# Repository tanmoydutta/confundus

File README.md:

# Confundus, an LIC Super Capacitor Trinket
Confundus powers an MCU driven LED matrix by means of using an LIC Super Capacitor as it's power source.

It also has a matching 3D printed box to house the circuit as a keychain hanger or as an ornament that hangs next to an ID card

Some of the actual view of the project - 

This project is certified as Open Source Hardware - 
<p align="center">
  
</p>

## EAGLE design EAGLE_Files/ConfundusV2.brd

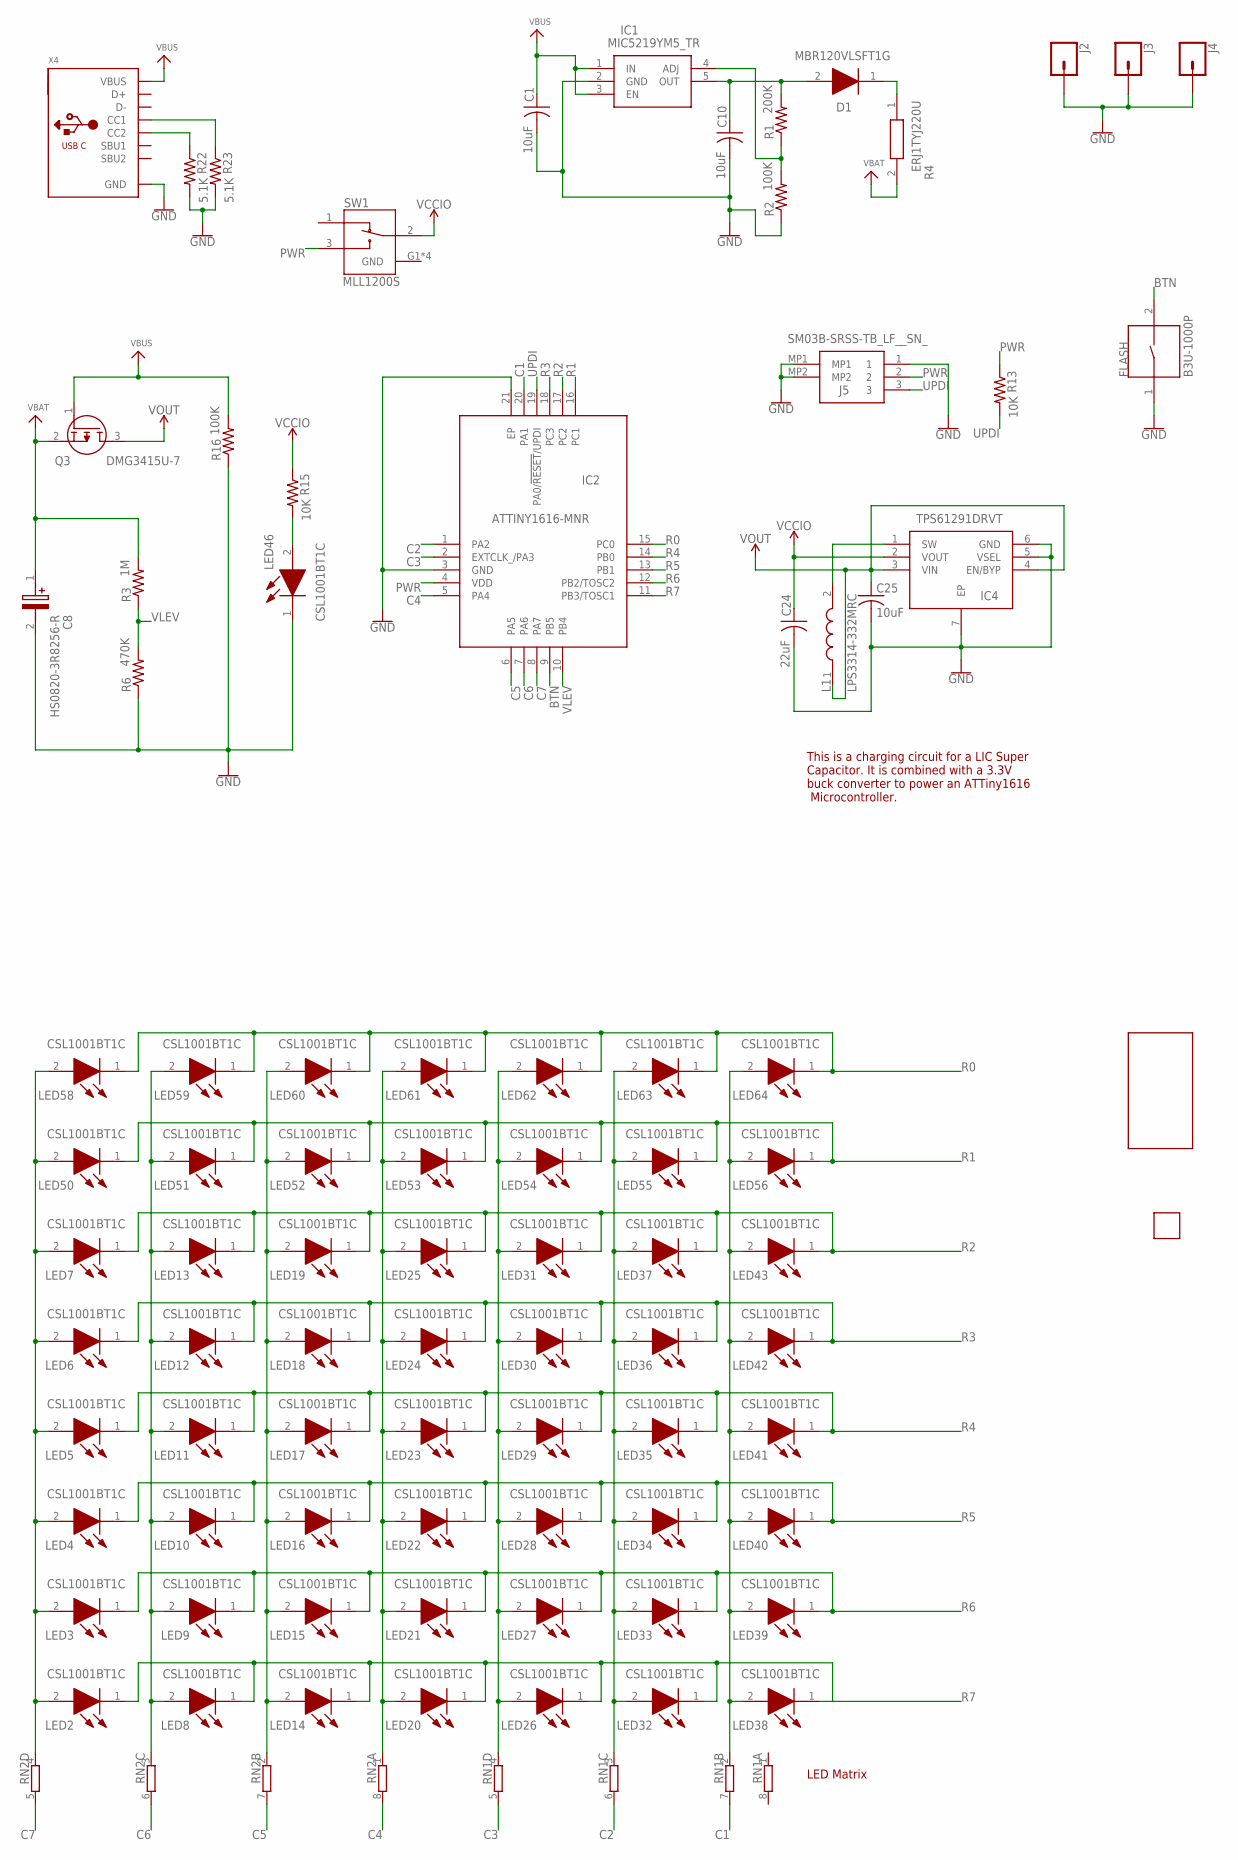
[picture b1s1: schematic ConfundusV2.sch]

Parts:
C1, C10, C25: 10uF; C0402
C8: HS0820-3R8256-R; CAPPRD350W65D850H2200
C24: 22uF; C0402
D1: MBR120VLSFT1G; SODFL3616X98N
FLASH: B3U-1000P; SW_B3U-1000P
IC1: MIC5219YM5_TR; SOT95P280X145-5N
IC2: ATTINY1616-MNR; QFN40P300X300X90-21N
IC4: TPS61291DRVT; SON65P200X200X80-7N
J2, J3, J4: CONN_01PTH_2MM; 1X01_2MM
J5: SM03B-SRSS-TB_LF__SN_; SM03BSRSSTBLFSN
L1: LPS3314-332MRC; LPS3314332MRC
LED2, LED3, LED4, LED5, LED6, LED7, LED8, LED9, LED10, LED11, LED12, LED13, LED14, LED15, LED16, LED17, LED18, LED19, LED20, LED21, LED22, LED23, LED24, LED25, LED26, LED27, LED28, LED29, LED30, LED31, LED32, LED33, LED34, LED35, LED36, LED37, LED38, LED39, LED40, LED41, LED42, LED43, LED46, LED50, LED51, LED52, LED53, LED54, LED55, LED56, LED58, LED59, LED60, LED61, LED62, LED63, LED64: CSL1001BT1C
Q3: DMG3415U-7; SOT96P240X100-3N
R1: 200K; R0402
R2, R16: 100K; R0402
R3: 1M; R0402
R4: ERJ1TYJ220U; ERJ1TRQF1R0U
R6: 470K; R0402
R13, R15: 10K; R0402
R22, R23: 5.1K; R0402
RN1, RN2: 4R-N0402ARV341; 4X0402ARV341
SW1: MLL1200S; SW_MLL1200S
U$1: SMARTT
U$2: SMARTT_SMALL
X4: MICROBUILDER_USB_C; MICROBUILDER_USB_C_CUSB31-CFM2AX-01-X

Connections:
BTN: FLASH.2, IC2.9 (PB5)
C1: IC2.20 (PA1), RN1.7 (2)
C2: IC2.1 (PA2), RN1.6 (2)
C3: IC2.2 (EXTCLK_/PA3), RN1.5 (2)
C4: IC2.5 (PA4), RN2.8 (2)
C5: IC2.6 (PA5), RN2.7 (2)
C6: IC2.7 (PA6), RN2.6 (2)
C7: IC2.8 (PA7), RN2.5 (2)
GND: C1.2, C8.2 (-), C10.2, C24.2, C25.2, FLASH.1, IC1.2 (GND), IC2.3 (GND), IC2.21 (EP), IC4.5 (VSEL), IC4.6 (GND), IC4.7 (EP), J2.1, J3.1, J4.1, J5.1, J5.MP1, J5.MP2, LED46.1 (K), R2.1, R6.1, R16.1, R22.2, R23.2, SW1.G1 (GND), SW1.G2 (GND), SW1.G3 (GND), SW1.G4 (GND), X4.A1B12 (GND), X4.B1A12 (GND)
unnamed: LED38.2 (A), LED39.2 (A), LED40.2 (A), LED41.2 (A), LED42.2 (A), LED43.2 (A), LED56.2 (A), LED64.2 (A), RN1.2 (1)
unnamed: LED32.2 (A), LED33.2 (A), LED34.2 (A), LED35.2 (A), LED36.2 (A), LED37.2 (A), LED55.2 (A), LED63.2 (A), RN1.3 (1)
unnamed: LED26.2 (A), LED27.2 (A), LED28.2 (A), LED29.2 (A), LED30.2 (A), LED31.2 (A), LED54.2 (A), LED62.2 (A), RN1.4 (1)
unnamed: LED20.2 (A), LED21.2 (A), LED22.2 (A), LED23.2 (A), LED24.2 (A), LED25.2 (A), LED53.2 (A), LED61.2 (A), RN2.1
unnamed: LED14.2 (A), LED15.2 (A), LED16.2 (A), LED17.2 (A), LED18.2 (A), LED19.2 (A), LED52.2 (A), LED60.2 (A), RN2.2 (1)
unnamed: LED8.2 (A), LED9.2 (A), LED10.2 (A), LED11.2 (A), LED12.2 (A), LED13.2 (A), LED51.2 (A), LED59.2 (A), RN2.3 (1)
unnamed: LED2.2 (A), LED3.2 (A), LED4.2 (A), LED5.2 (A), LED6.2 (A), LED7.2 (A), LED50.2 (A), LED58.2 (A), RN2.4 (1)
unnamed: R22.1, X4.B5 (CC2)
unnamed: R23.1, X4.A5 (CC1)
unnamed: C10.1, D1.2 (A), IC1.5 (OUT), R1.2
unnamed: IC1.4 (ADJ), R1.1, R2.2
unnamed: D1.1 (K), R4.1
unnamed: IC4.1 (SW), L1.2
unnamed: LED46.2 (A), R15.2
PWR: IC2.4 (VDD), J5.2, R13.1, SW1.3
R0: IC2.15 (PC0), LED58.1 (K), LED59.1 (K), LED60.1 (K), LED61.1 (K), LED62.1 (K), LED63.1 (K), LED64.1 (K)
R1: IC2.16 (PC1), LED50.1 (K), LED51.1 (K), LED52.1 (K), LED53.1 (K), LED54.1 (K), LED55.1 (K), LED56.1 (K)
R2: IC2.17 (PC2), LED7.1 (K), LED13.1 (K), LED19.1 (K), LED25.1 (K), LED31.1 (K), LED37.1 (K), LED43.1 (K)
R3: IC2.18 (PC3), LED6.1 (K), LED12.1 (K), LED18.1 (K), LED24.1 (K), LED30.1 (K), LED36.1 (K), LED42.1 (K)
R4: IC2.14 (PB0), LED5.1 (K), LED11.1 (K), LED17.1 (K), LED23.1 (K), LED29.1 (K), LED35.1 (K), LED41.1 (K)
R5: IC2.13 (PB1), LED4.1 (K), LED10.1 (K), LED16.1 (K), LED22.1 (K), LED28.1 (K), LED34.1 (K), LED40.1 (K)
R6: IC2.12 (PB2/TOSC2), LED3.1 (K), LED9.1 (K), LED15.1 (K), LED21.1 (K), LED27.1 (K), LED33.1 (K), LED39.1 (K)
R7: IC2.11 (PB3/TOSC1), LED2.1 (K), LED8.1 (K), LED14.1 (K), LED20.1 (K), LED26.1 (K), LED32.1 (K), LED38.1 (K)
UPDI: IC2.19 (PA0/!RESET!/UPDI), J5.3, R13.2
VBAT: C8.1 (+), Q3.2 (S), R3.2, R4.2
VBUS: C1.1, IC1.1 (IN), IC1.3 (EN), Q3.1 (G), R16.2, X4.A4B9 (VBUS), X4.B4A9 (VBUS)
VCCIO: C24.1, IC4.2 (VOUT), R15.1, SW1.2
VLEV: IC2.10 (PB4), R3.1, R6.2
VOUT: C25.1, IC4.3 (VIN), IC4.4 (EN/BYP), L1.1, Q3.3 (D)

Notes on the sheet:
LED Matrix
This is a charging circuit for a LIC Super Capacitor. It is combined with a 3.3V buck converter to power an ATTiny1616 Microcontroller.

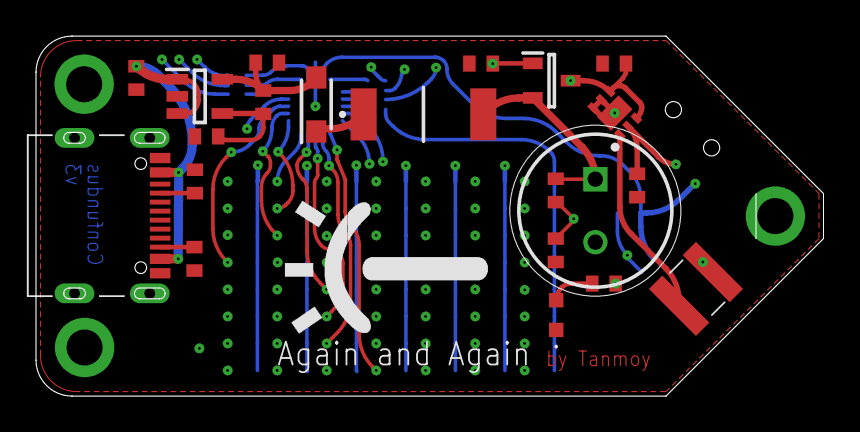
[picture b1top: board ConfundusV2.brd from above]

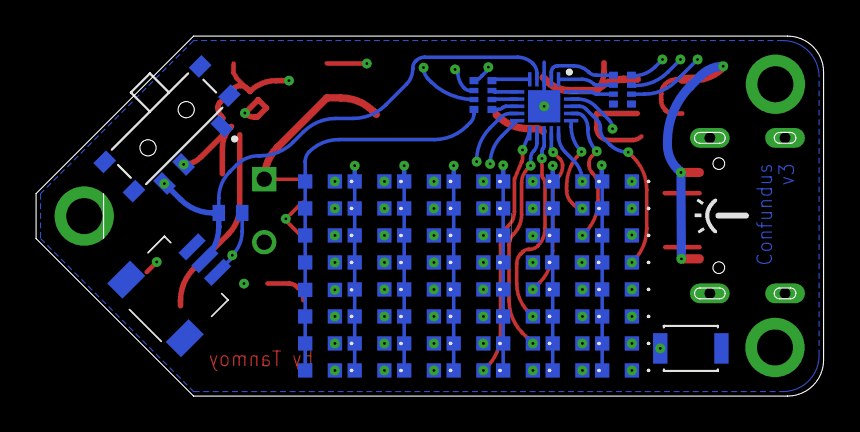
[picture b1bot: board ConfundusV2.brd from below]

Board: 6 copper layers, 43.7 x 20.0 mm, 89 parts (63 on the bottom side), 38 nets.

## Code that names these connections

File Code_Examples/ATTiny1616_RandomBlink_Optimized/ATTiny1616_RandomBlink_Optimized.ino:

#include <avr/sleep.h>
#include <avr/interrupt.h>

// Row pins
const uint8_t rowPins[8] = {
  PIN_PC0, PIN_PC1, PIN_PC2, PIN_PC3,
  PIN_PB0, PIN_PB1, PIN_PB2, PIN_PB3
};

// Column pin
const uint8_t colPin = PIN_PA1;

volatile bool wakeFlag = false;

void setup() {
  allHiZ();

  ADC0.CTRLA &= ~ADC_ENABLE_bm;
  AC0.CTRLA  &= ~AC_ENABLE_bm;

  randomSeed(analogRead(0));

  setupRTC();

  set_sleep_mode(SLEEP_MODE_PWR_DOWN);
}

void loop() {

  if (!wakeFlag) {
    sleep_mode();
  }

  wakeFlag = false;

  // Let boost stabilize
  delay(1);

  // ✨ Burst of sparkles
  for (uint8_t i = 0; i < 4; i++) {

    uint8_t r = random(0, 8);

    lightOne(r);
    delay(5);     // ON time

    allHiZ();
    delay(20);    // short gap between sparkles
  }
}

// Turn on one LED
void lightOne(uint8_t row) {
  allHiZ();

  pinMode(colPin, OUTPUT);
  digitalWrite(colPin, HIGH);

  pinMode(rowPins[row], OUTPUT);
  digitalWrite(rowPins[row], LOW);
}

// Hi-Z all pins
void allHiZ() {
  pinMode(colPin, INPUT);

  for (uint8_t i = 0; i < 8; i++) {
    pinMode(rowPins[i], INPUT);
  }
}

// RTC setup (~2 sec)
void setupRTC() {
  while (RTC.STATUS > 0);

  RTC.CLKSEL = RTC_CLKSEL_INT1K_gc;
  RTC.PITINTCTRL = RTC_PI_bm;

  RTC.PITCTRLA = RTC_PERIOD_CYC2048_gc | RTC_PITEN_bm;

  sei();
}

ISR(RTC_PIT_vect) {
  RTC.PITINTFLAGS = RTC_PI_bm;
  wakeFlag = true;
}

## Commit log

2026-04-20 Adding directory structure
2026-05-05 Adding license information and documentation
2026-05-05 Revise README with title and project details
    Updated project title and added description with images.
2026-05-05 Adding images
2026-05-05 Update README with details on 3D printed box
    Added information about the 3D printed box for the circuit.
2026-05-07 Update Read me for new images
2026-05-09 new images
2026-05-14 Adjustement to the charging circuit
2026-05-20 Adding OSHWA mark
2026-05-21 Readme update
2026-06-12 Updating the circuit adjustments for introduction of a Schottky diode

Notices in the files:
parts and their libraries:
SparkFun-Connectors: Licensing: Creative Commons ShareAlike 4.0 International - https://creativecommons.org/licenses/by-sa/4.0
